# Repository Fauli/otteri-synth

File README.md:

# Otteri-synth

<p align="center">
    
    <br/>
    Cause otters like to play!
</p>

## Table of Contents

- [Otteri-synth](#otteri-synth)
  - [Table of Contents](#table-of-contents)
- [Introduction](#introduction)
- [Design](#design)
- [Hardware](#hardware)
  - [Parts List](#parts-list)
  - [Case](#case)
  - [Microcontroller](#microcontroller)
  - [Amplifier \& speakers](#amplifier--speakers)
  - [Power management](#power-management)
  - [Wiring diagram](#wiring-diagram)
  - [Final print config](#final-print-config)
  - [Putting it all together](#putting-it-all-together)
    - [KiCad](#kicad)
  - [Importing Teensy into KiCad](#importing-teensy-into-kicad)
  - [Schematics and PCB design](#schematics-and-pcb-design)
  - [Implementation using Perf Board](#implementation-using-perf-board)
  - [Ground loop](#ground-loop)
  - [Finished product](#finished-product)
    - [Final Project Files](#final-project-files)
- [Software](#software)
- [Demo](#demo)
- [Personal conclusion \& learnings](#personal-conclusion--learnings)

# Introduction
For fun I wanted to create a synthesizer that looks like an otter. It should be my daughters first synth :)

In these modern times I wanted to leverage what new tools have been available to design this project. In my mind I had a clear vision how the synth should look and play. I never did such a project before, so it was also a learning experience for me.

# Design
As the base I generated an image using [DALL-E](https://openai.com/index/dall-e-2/) and fed it into [TRELLIS](https://huggingface.co/JeffreyXiang/TRELLIS-image-large).

The prompt was:
```bash
Create a prototype of a synthesizer case.
White background, it is important that there is no background at all in the image. Should be childrens style, cool design and possible to 3d print on a 3d printer. I want to actually implement the case and use it for a synth project.
The synth should somewhat look like an otter.

# after some back and forth with some prototypes that had too many hands :P
There are too many hands, start over with an otter design, surprise me with a new and cool idea
```

In the end I was able to create an image in DALL-E that exactly matched what I had in mind.

TRELLIS created an amazing mesh out of it that I could directly use as a starting point in [Blender](https://www.blender.org/).
You can find and download the mesh [here](.attachements/otteri-synth-generated.glb).

I then adapted the generated mesh to my liking and needs.

# Hardware

Because I have a 3d printer, the case and inner works was specially made for this synth.

## Parts List

Here is a quick overview of the used parts. A detailed description can be found below.

| Part                       | Amount | Description                                   |
| -------------------------- | ------ | --------------------------------------------- |
| 3D Printed Case            | 1      | Custom case to house all components           |
| Teensy 3.2                 | 1      | Microcontroller for handling audio processing |
| Teensy Audio Shield        | 1      | Audio processing shield for Teensy            |
| Adafruit MAX7944           | 1      | Amplifier for driving the speakers            |
| 4Ohm 5W 40mm Speakers      | 2      | Small speakers for audio output               |
| Arcade Buttons             | 10     | Durable buttons for user interaction          |
| DC-015 circular power plug | 1      | Power plug for the synth                      |
| M5Stack Buck Converter 5 V | 1      | 12V to 5V converter for Teensy power          |
| Ground Loop isolator       | 1      | Prevent hum sound in speaker                  |
| Various Wires              | -      | Wiring for connecting all components          |

## Case

The initial prototype was small, but after confirming its success, I scaled up the design to accommodate robust electronics suitable for a child's enthusiastic use. 

I opted for durable arcade buttons to withstand frequent interaction.

## Microcontroller

The core of the Otteri-synth is powered by a [Teensy 3.2](https://www.pjrc.com/store/teensy32.html) with the [Teensy Audio Shield](https://www.pjrc.com/store/teensy3_audio.html) as I still had them laying around at home.

The Teensy is excellent for synthesizer projects due to its high-performance ARM Cortex-M4 processor and real-time audio processing capabilities,

I'm a big fan of the teensy boards!

## Amplifier & speakers

Another component I still had laying around at home was an [Adafruit MAX7944](https://www.adafruit.com/product/1752) amplifier. For the speakers size, this will be more then enough.

As speakers I'm using 2 4Ohm 3W 40mm. They might be a little small, but should do the job.

## Power management

Teensy supports 5V power input, the amplifier needs 12V. In order to now have 2 inputs for power, I'm using a [Buck Converter - U125 - ME3116AM6G Step-Down Voltage Converter Unit, 5V, 1A](https://www.distrelec.ch/en/me3116am6g-step-down-voltage-converter-unit-5v-1a-m5stack-u125/p/30230761) to have the 12V shared input stepped down to 5V for the teensy:

```

          +---------------+
          |  12V Supply   |
          +---------------+
                |   |
                |   | 
         +------+   +------+  
         |                 |
  [Buck Converter]         |  
         |                 |
      5V Output        12V Output
         |                 |
   +-----+----+      +-----+-----+
   |  Teensy  |      | Amplifier |
   |   3.2    |      | (MAX9744) |
   +----------+      +-----------+
         |                 |
         +-- Common Ground --------+
```

To be able to re-use standard 12V power adapters, I prepared a hole at the back of the synth and added a circular power plug.

## Wiring diagram

| Button   | Pin | Description                             |
| -------- | --- | --------------------------------------- |
| Button 0 | 0   | Play note C                             |
| Button 1 | 1   | Play note D                             |
| Button 2 | 2   | Play note E                             |
| Button 3 | 3   | Play note F                             |
| Button 4 | 4   | Play note G                             |
| Button 5 | 5   | Play note A                             |
| Button 6 | 8   | Play note B                             |
| Button 7 | 21  | Play note C                             |
| Button 8 | 20  | Change preset (instrument) + volume     |
| Button 9 | 17  | Change octave + volume                  |

*Additional note:* I added the functionality to change the volume by holding down Button 8 and Button 9 simultaneously and then changing the volume down or up with Button 0 and Button 1.

## Final print config

The first half I printed had way too small dowels. So they ended up breaking when being inserted into the body. 

So in try 2, I cut the Otter in Bambu Studio, using hexagons dowels with length 2cm and 1.5cm diameter as connectors. Initially I had a small gap between the two pieces. So I manually reduced the length of the dowels and re-printed just these.

**TODO: Add 3mf file of project...**

## Putting it all together

A first circuit prototype was made with a breadboard and some initial buttons I had still at home. The order for the remaining buttons was on it's way.

To fix the plate with the buttons to the body of the synth, I got melt threads in M3 size, like these:

In Blender I prepared the matching 4mm holes to fix the threads in.

The first full print was a success (even if the filament ran out and I had to switch to a different color to finish the print). I was able to verify my design and continue with the final hardware steps.

I had to change the speaker because my initial one sounded very bad. The new one had holes on the side to proper fix the speaker to the case.

### KiCad

Initially I had the idea to create and print a custom PDB for this project.
But after designing it and realizing the simplicity, I went with a prefboard setup.

Nevertheless, I went through the steps of creating the project and gerber files for the synth in Kicad as a learning excercise.
I started with importing the footpint into KiCad, arranging the schematics and drawing the PCB.

## Importing Teensy into KiCad
Download Teensy files from:
* [Teensy Library](https://github.com/XenGi/teensy_library)
* [Teensy.Pretty](https://github.com/XenGi/teensy.pretty)

And add them following these steps:

1. Open the Footprint Editor: From the main window in KiCad, navigate to Tools > Footprint Editor.
2. Manage Footprint Libraries (Symbol in the opened window):
    1. Within the Footprint Editor, go to Preferences > Manage Footprint Libraries....
    You’ll see two tabs: "Global Libraries" (libraries available to all projects) and "Project Specific Libraries" (libraries only available to the current project).
    2. To add a new library, click the “+” button under the appropriate tab.
    Point the file browser to the directory containing your .kicad_mod files. Select this directory as your library directory and provide a nickname for easy reference.
    3. Confirm your addition by clicking "OK".

Step 2: Manage Symbol Libraries

1. Access the Library Management:
    In the Symbol Editor, go to Preferences > Manage Symbol Libraries....
    This opens the Symbol Libraries Manager where you can add, remove, or modify symbol libraries.

1. Add a New Library:
    1. Click on the "Project Specific Libraries" tab to add the library only to your current project, or choose the "Global Libraries" tab to add the library to all KiCad projects on your system.
    1. Click the ‘+’ button at the bottom of the window to add a new library entry.

1. Specify Library Details:
    1. Nickname: Enter a nickname for the library. This nickname will be used to reference the library within KiCad.
    1. Library Path: Click on the folder icon next to the ‘Library Path’ field to browse to the location where you extracted your .lib file. Select the .lib file.
    1. Plugin Type: Ensure the plugin type is set to ‘Legacy’ for .lib files.
    The .dcm file, if located in the same directory, will automatically be linked for documentation purposes, so there's no need to do anything extra for it.

1. Confirm and Close:
    1. After entering all details, click “OK” to add the library.
    1. Close the Library Manager by clicking "OK" again.

## Schematics and PCB design

The schematics is created according the planned out pin setup above.

Out of the schematics, I was able to create an initial, simple PCB design.

The files can be downloaded here:
* [Schematics](.attachements/otteri-synth.kicad_sch)
* [PCB Design](.attachements/otteri-synth.kicad_pcb)

## Implementation using Perf Board

Because the board was so simple, I ended up using a perf board and did the manual path setup using solder. 

It does not look very nice, but works well and is sturdy.

Completed plate setup with all buttons attached.

Inside of the finished otter.

## Ground loop

After I connected the setup and switched the power supply of the teensy from USB to the stepped down 5V VIN, i had a constant hum on the speakers.

This is called a ground loop. A ground loop occurs when multiple devices share more than one path to ground, creating an unintended loop.

In my case this was the commong ground of the power as well as the audio jack cable.

Top combat this I used a ground loop isolator. This fixed the problem.

## Finished product

Top view of the synth.

Side view of the synth.

Back view of the synth, with the power plug.

### Final Project Files

You can find the [blender project](.attachements/otteri-synth-v6.blend) and the [3d STL file](.attachements/otteri-synth-v6.stl) in in the repo.

# Software

The project began with basic sketches in the Arduino IDE, but as the software evolved, I transitioned to [PlatformIO](https://platformio.org/) for enhanced code management and scalability.

The complete codebase is available in the `otteri-synth-code` directory.

I wanted to have multiple voices, in order to be able to not only play 1 key at a time. This was done by mutiplying the whole virtual audio setup 3 times and defining a common output to i2s.

I'm making heavy use of the [Teensy Audio Library](https://www.pjrc.com/teensy/td_libs_Audio.html) library.

# Demo

A demo of the sounds it makes before it got assambled: [Pre-assembly demo video](.attachements/first-demo.mov).

# Personal conclusion & learnings

This project was incredibly rewarding and enjoyable, serving not only as a creative outlet but also as a significant learning experience.

Throughout the process, I deepened my understanding of hardware integration, 3D printing nuances, and audio electronics.

Iterating through multiple prototypes highlighted the importance of adaptability, particularly when refining the 3D design and addressing unexpected technical challenges, such as the ground loop issue.

The synth turned out exactly as envisioned - playful, robust, and inviting to young hands eager to explore music. I'm excited to see how my daughter interacts with the Otteri-synth, and I'm hopeful it sparks a lasting curiosity and joy for music creation.

Future projects are already planned. Next time with more advanced controls and the Teensy 4.1 as controller.

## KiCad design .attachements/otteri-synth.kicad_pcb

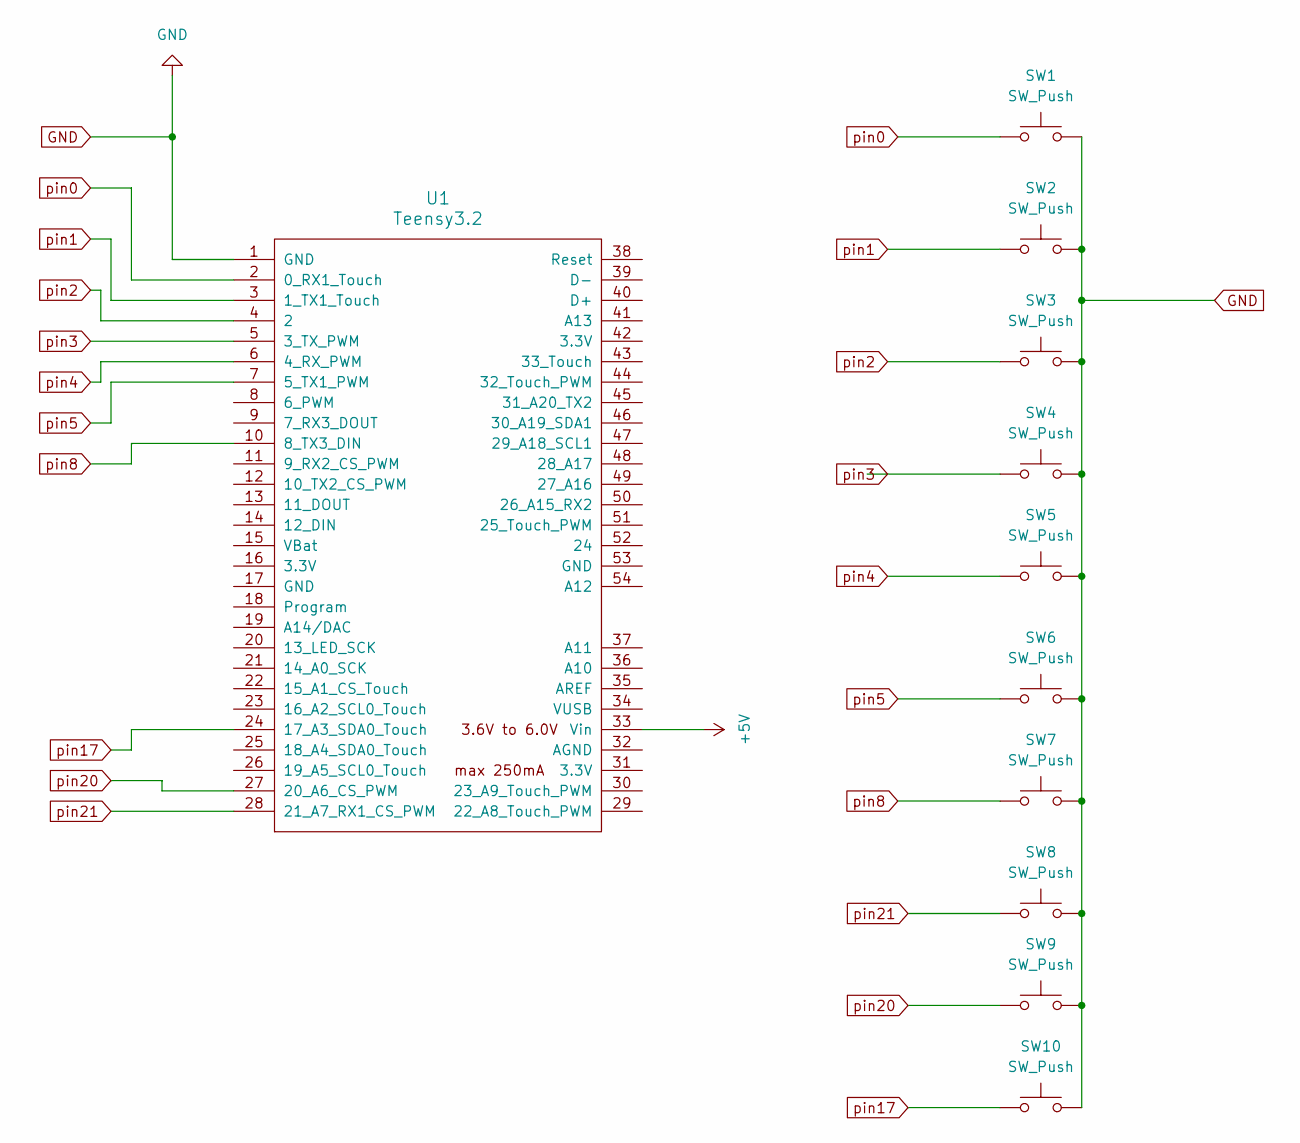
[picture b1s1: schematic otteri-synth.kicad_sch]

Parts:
SW1, SW2, SW3, SW4, SW5, SW6, SW7, SW8, SW9, SW10: SW_Push; PinHeader_1x02_P2.54mm_Vertical
U1: Teensy3.2; Teensy30_31_32_All_Pins

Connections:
+5V: U1.33 (Vin)
GND: SW1.2, SW2.2, SW3.2, SW4.2, SW5.2, SW6.2, SW7.2, SW8.2, SW9.2, SW10.2, U1.1 (GND)
pin0: SW1.1, U1.2 (0_RX1_Touch)
pin1: SW2.1, U1.3 (1_TX1_Touch)
pin2: SW3.1, U1.4 (2)
pin3: SW4.1, U1.5 (3_TX_PWM)
pin4: SW5.1, U1.6 (4_RX_PWM)
pin5: SW6.1, U1.7 (5_TX1_PWM)
pin8: SW7.1, U1.10 (8_TX3_DIN)
pin17: SW10.1, U1.24 (17_A3_SDA0_Touch)
pin20: SW9.1, U1.27 (20_A6_CS_PWM)
pin21: SW8.1, U1.28 (21_A7_RX1_CS_PWM)

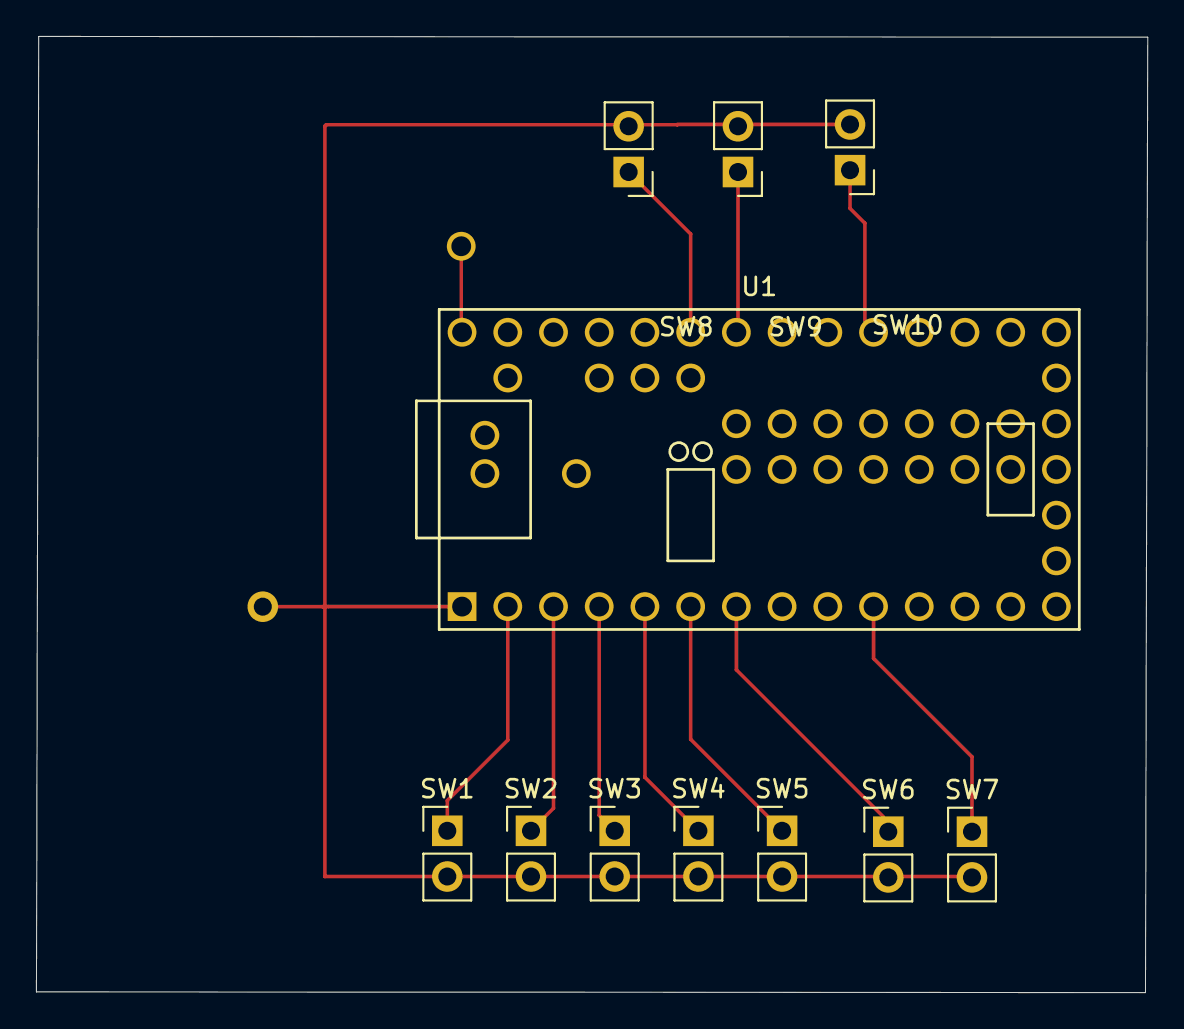
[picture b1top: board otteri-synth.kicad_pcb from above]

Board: 2 copper layers, 61.7 x 53.1 mm, 11 parts (0 on the bottom side), 11 nets.

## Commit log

2025-01-17 add some logic
2025-01-17 add some logo
2025-01-18 moved to platformIO
2025-01-18 buttons work
2025-01-18 rewind, start again
2025-01-19 add images and README
2025-01-19 link image in README
2025-01-19 rework README
2025-01-20 works now
2025-01-21 finally have multiple voices working
2025-01-21 addeed cents
2025-01-22 added readme stuff
2025-02-12 next version
2025-02-13 upload initial video
2025-02-13 resize image
2025-02-13 add KiCad files
2025-02-15 add prompt
2025-03-23 add infos to README
